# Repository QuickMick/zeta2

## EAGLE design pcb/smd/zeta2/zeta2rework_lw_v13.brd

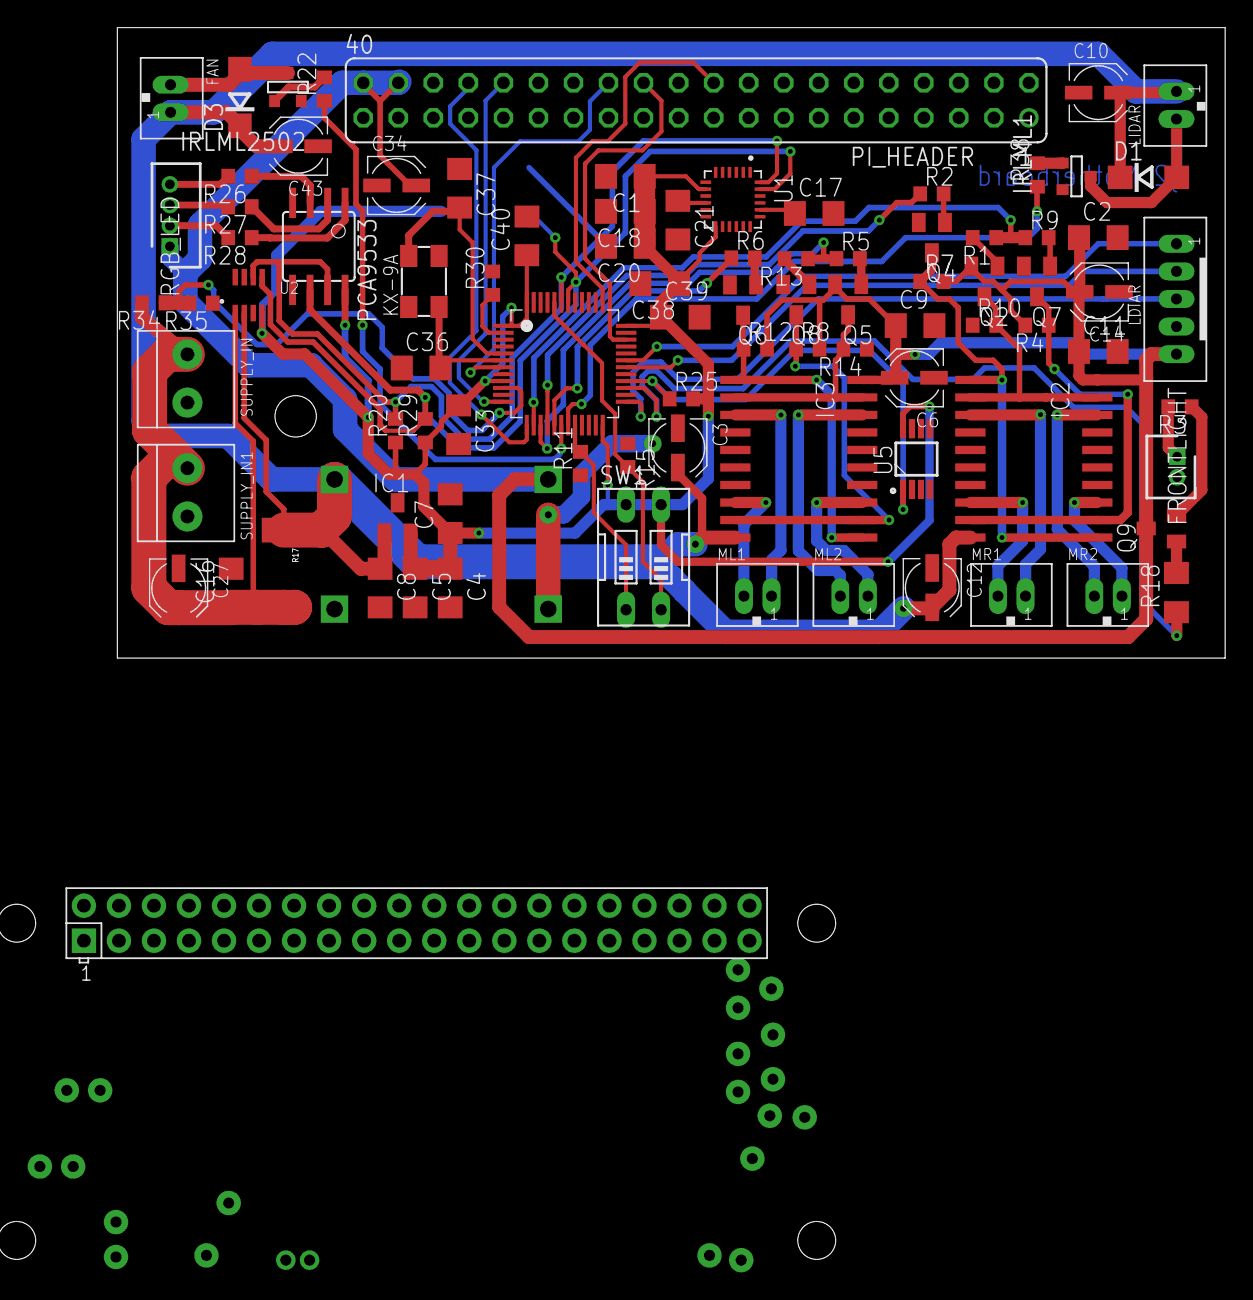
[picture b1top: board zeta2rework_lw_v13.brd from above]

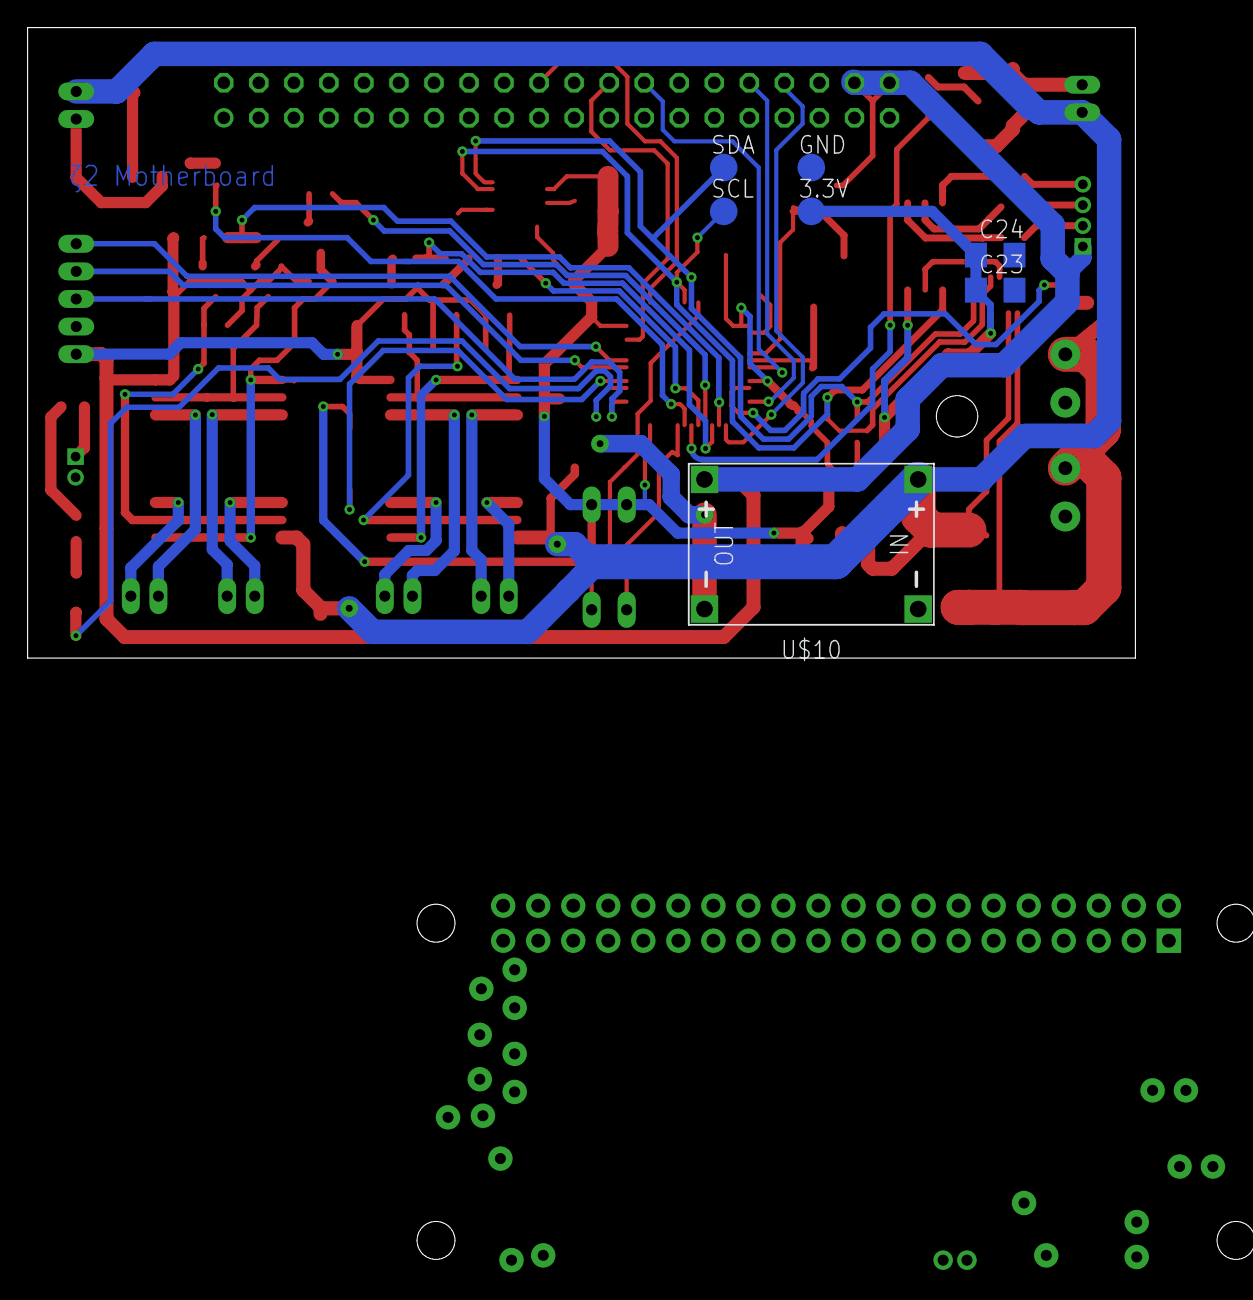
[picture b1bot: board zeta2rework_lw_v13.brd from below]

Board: 2 copper layers, 80.3 x 45.7 mm, 96 parts (7 on the bottom side), 64 nets.

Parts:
3.3V: TPSQTP20R; TP20R
C1, C4, C23, C36, C37: 10µF; C1206
C2, C9: 0.1nF; C1206
C3, C10, C12, C27, C34, C43: 47µF; UD-4X5,8_NICHICON
C5, C7, C11, C16, C18, C20, C21, C24: 0.1µF; C1206
C6, C14: 10µF; UD-4X5,8_NICHICON
C8: 4.7µF; C1206
C17: 2,2nF; C1206
C33, C38, C39, C40: 10nF; C1206
D1, D3: 1N4004 SMD; DO214AC
FAN: JST-PH_2-PIN_HEADER; JST_B2B-PH_HEADER
FRONTLIGHT: B2B-ZR(LF)(SN); SHDR2W50P0X150_1X2_450X350X450
GND: TPSQTP20R; TP20R
IC1: MAX6520; SOT23
IC2, IC3: L293DD; SO20
IRLML1, IRLML2502: SOT-23
KX-9A: 8Mhz; 5.0X3.2_KX-9A
LDIAR: JST-PH_5-PIN_HEADER; JST_B5B-PH_HEADER
LIDAR: JST-PH_2-PIN_HEADER; JST_B2B-PH_HEADER
ML1, ML2: JST-PH_2-PIN_HEADER; JST_B2B-PH_HEADER
MR1, MR2: JST-PH_2-PIN_HEADER; JST_B2B-PH_HEADER
PCA9533: PCA9533; SOIC8
PI_HEADER: FE20-2
Q2, Q4, Q5, Q6, Q7, Q8, Q9: SOT23
R1, R2, R5, R6, R9, R13: 500R; R0603
R3, R26, R27, R28: 220R; R0603
R4, R7, R8, R10, R12, R14, R30, R34: 100k; R0603
R11, R15: 132k; R0603
R17: 0.1/1% (PT2512FK-070R1L); 2512
R18: 500; R1206
R20, R29: 10k; R0603
R22, R38: 22R; R0603
R25: 4k7; R0603
R35: 69k; R0603
RGB_LED: B4B-ZR(LF)(SN); SHDR4W50P0X150_1X4_750X350X450
SCL: TPSQTP20R; TP20R
SDA: TPSQTP20R; TP20R
STM32F103CB: STM32F103CB; LQFP48_7X7MM_0.5MMPP
SUPPLY_IN, SUPPLY_IN1: TERMBLOCK_1X2-3.5MM; 1X2-3.5MM
SW1: EDG-02
U1: MPU-6050; QFN50P400X400X95-24N
U2: INA219; SOT23-8
U5: DS18B20U+; SOP65P490X95-8N
U$1: RPI-ZERO; RASP_PI_ZERO_BOARD_FULL
U$10: DC-DC-STEP-DOWN-MP2307

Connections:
+3V3: 3.3V.TP, C1.1, C4.1, C5.1, C7.1, C18.1, C20.1, C23.1, C24.1, C33.1, C38.1, C39.1, C40.1, IC1.2, PCA9533.8, R20.1, R25.2, R29.1, STM32F103CB.1, STM32F103CB.9, STM32F103CB.24, STM32F103CB.36, STM32F103CB.48, SW1.3, SW1.4, U1.8, U1.13, U2.4, U5.8
+5V: C2.1, C6.+, C9.1, C11.1, C14.+, C34.+, IC2.20, IC3.20, LDIAR.P5, PI_HEADER.38, PI_HEADER.40, Q2.2, Q5.2, Q9.3, R4.2, R7.2, R8.2, R12.2, RGB_LED.1, U$10.OUT+
+8V: C3.+, C8.1, C10.+, C12.+, C43.+, D1.C, D3.C, FAN.P1, IC1.1, IC2.10, IC3.10, LIDAR.P1, R17.1, U2.2, U$10.IN+
BAT_LVL: R34.1, R35.2, STM32F103CB.10
BOOT0: R15.2, STM32F103CB.44, SW1.2
BOOT1: R11.2, STM32F103CB.20, SW1.1
FRONT_LIGHT: R18.1, STM32F103CB.27
GND: C1.2, C2.2, C3.-, C4.2, C5.2, C6.-, C7.2, C8.2, C9.2, C10.-, C11.2, C12.-, C14.-, C16.2, C17.2, C18.2, C20.2, C21.2, C23.2, C24.2, C27.-, C33.2, C34.-, C36.1, C37.1, C38.2, C39.2, C40.2, C43.-, FRONTLIGHT.2, GND.TP, IC1.3, IC2.4, IC2.5, IC2.6, IC2.7, IC2.14, IC2.15, IC2.16, IC2.17, IC3.4, IC3.5, IC3.6, IC3.7, IC3.14, IC3.15, IC3.16, IC3.17, IRLML1.2, IRLML2502.2, LDIAR.P4, PCA9533.4, PI_HEADER.1, PI_HEADER.8, PI_HEADER.12, PI_HEADER.15, PI_HEADER.22, PI_HEADER.28, PI_HEADER.31, PI_HEADER.36, Q4.2, Q6.2, Q7.2, Q8.2, R10.1, R11.1, R14.1, R15.1, R30.2, R35.1, STM32F103CB.8, STM32F103CB.23, STM32F103CB.35, STM32F103CB.47, SUPPLY_IN.1, SUPPLY_IN1.1, U1.1, U1.9, U1.11, U1.18, U2.3, U2.7, U2.8, U5.4, U$10.IN-, U$10.OUT-
LIDAR_POS_INT: LDIAR.P3, STM32F103CB.25
M_DIR_1: R1.1, R9.1, STM32F103CB.14
M_DIR_2: R5.1, R13.1, STM32F103CB.15
unnamed: IC2.9, IC2.12, Q7.3, R4.1
unnamed: IC3.18, ML2.P2
unnamed: IC3.13, ML2.P1
unnamed: IC2.18, MR2.P2
unnamed: IC2.2, IC2.19, Q2.3, R10.2
unnamed: IC3.9, IC3.12, Q8.3, R8.1
unnamed: IC3.2, IC3.19, Q5.3, R14.2
unnamed: IC2.1, IC2.11, Q4.3, R7.1
unnamed: IC3.1, IC3.11, Q6.3, R12.1
unnamed: Q2.1, R1.2
unnamed: Q4.1, R2.2
unnamed: Q7.1, R9.2
unnamed: Q5.1, R5.2
unnamed: Q6.1, R6.2
unnamed: Q8.1, R13.2
unnamed: IC2.13, MR2.P1
unnamed: IC2.8, MR1.P2
unnamed: IC2.3, MR1.P1
unnamed: Q9.1, R18.2
unnamed: PCA9533.3, R26.1
unnamed: PCA9533.2, R27.1
unnamed: PCA9533.1, R28.1
unnamed: IC3.8, ML1.P2
unnamed: IC3.3, ML1.P1
unnamed: Q9.2, R3.1
unnamed: FRONTLIGHT.1, R3.2
unnamed: R26.2, RGB_LED.4
unnamed: R27.2, RGB_LED.3
unnamed: C17.1, U1.20
unnamed: R28.2, RGB_LED.2
unnamed: C21.1, U1.10
unnamed: IRLML2502.3, R22.2
unnamed: IRLML1.3, R38.2
unnamed: D1.A, IRLML1.1, LIDAR.P2
unnamed: C36.2, KX-9A.1, STM32F103CB.6
unnamed: C37.2, KX-9A.3, STM32F103CB.5
unnamed: R30.1, STM32F103CB.2
unnamed: D3.A, FAN.P2, IRLML2502.1
NRST: PI_HEADER.26, STM32F103CB.7
PWM_FAN: R22.1, STM32F103CB.18
PWM_LIDAR: R38.1, STM32F103CB.19
PWM_M_EN_1: R2.1, STM32F103CB.16
PWM_M_EN_2: R6.1, STM32F103CB.17
SCL: PCA9533.6, R29.2, SCL.TP, STM32F103CB.42, U1.23, U2.5
SDA: PCA9533.7, R20.2, SDA.TP, STM32F103CB.43, U1.24, U2.6
SWCLK: PI_HEADER.20, STM32F103CB.37
SWDIO: PI_HEADER.24, STM32F103CB.34
TEMPERATURE: R25.1, STM32F103CB.28, U5.1
U1_RX: LDIAR.P1, STM32F103CB.31
U1_TX: LDIAR.P2, STM32F103CB.30
USART2_RX: PI_HEADER.34, STM32F103CB.13
USART2_TX: PI_HEADER.32, STM32F103CB.12
V+: C16.1, C27.+, R17.2, R34.2, SUPPLY_IN.2, SUPPLY_IN1.2, U2.1

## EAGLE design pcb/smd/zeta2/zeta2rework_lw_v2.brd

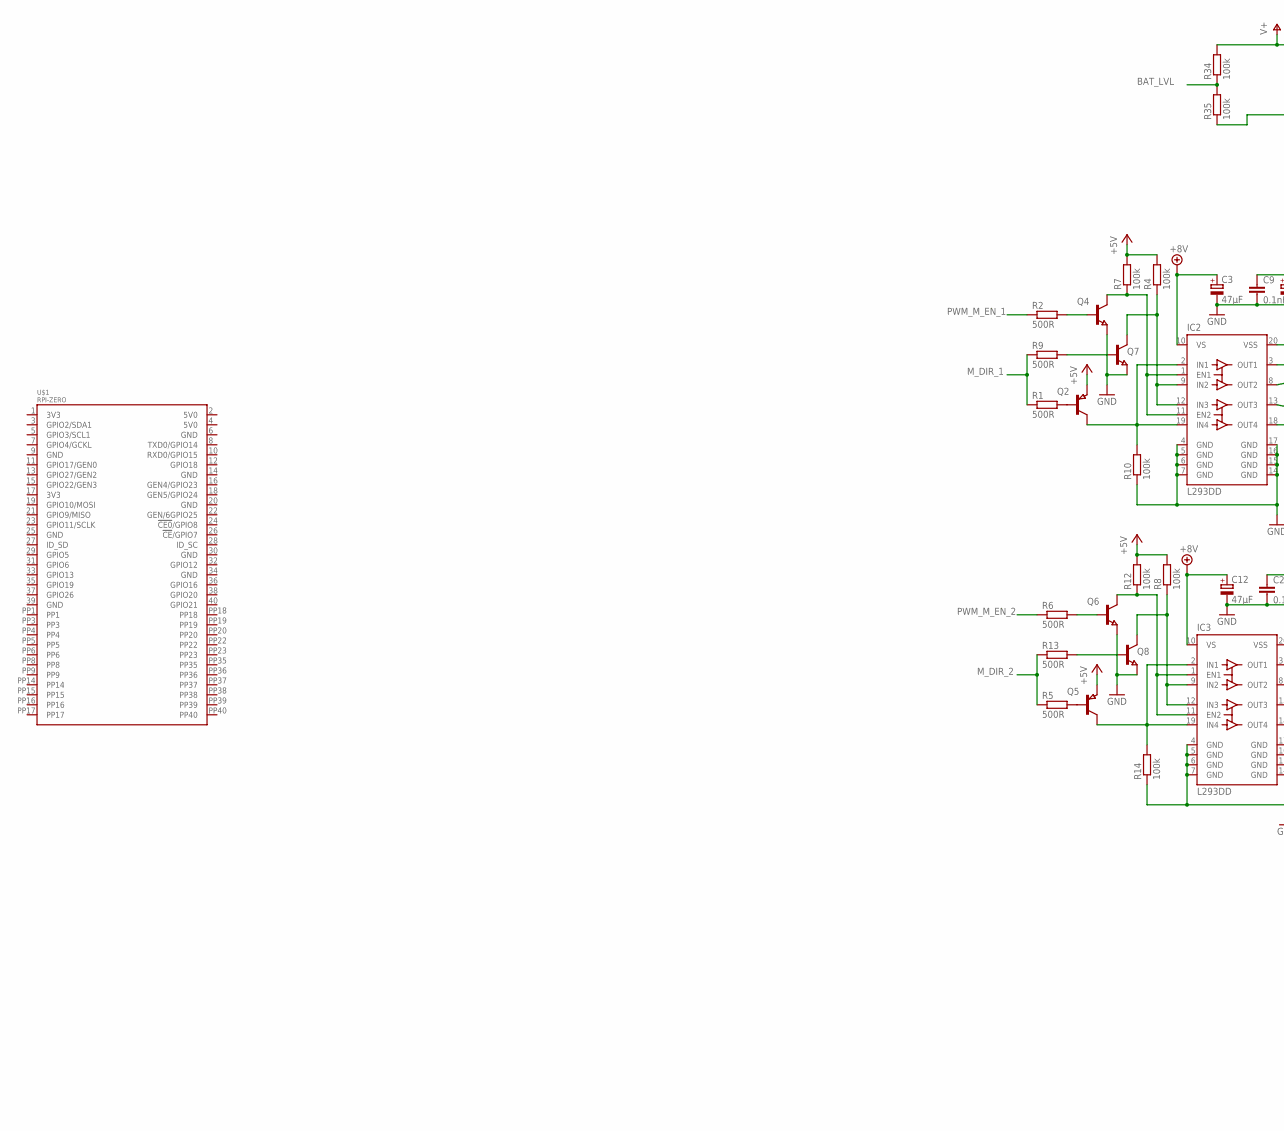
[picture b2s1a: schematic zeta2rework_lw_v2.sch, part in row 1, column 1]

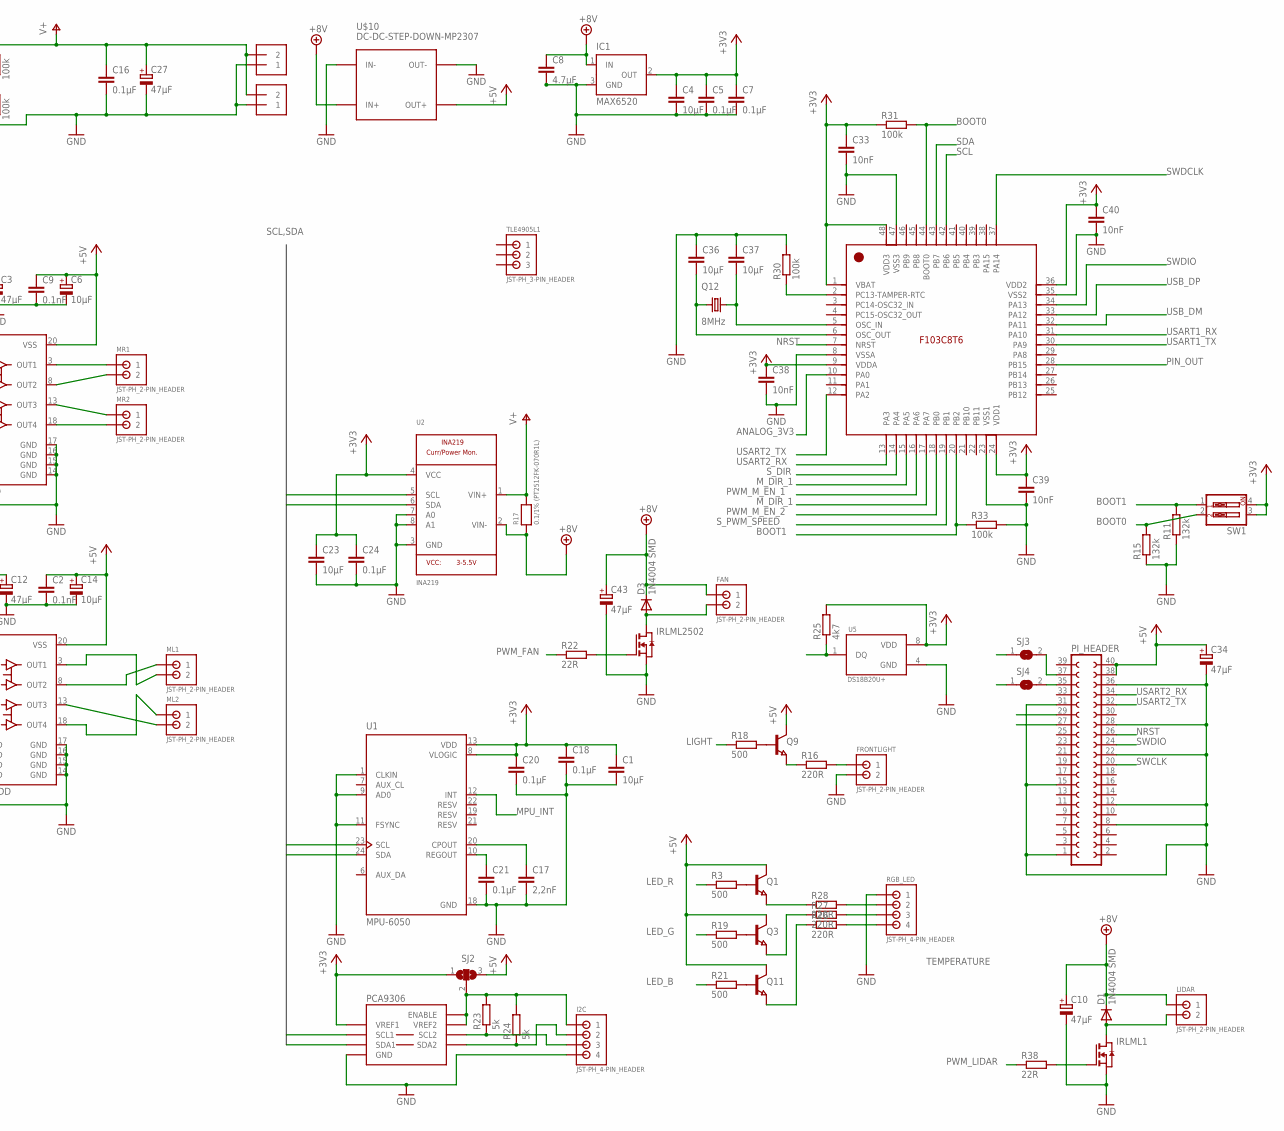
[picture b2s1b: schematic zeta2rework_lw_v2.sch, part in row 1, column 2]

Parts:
C1, C4, C23, C36, C37: 10µF; C1206
C2, C9: 0.1nF; C1206
C3, C10, C12, C27, C34, C43: 47µF; UD-4X5,8_NICHICON
C5, C7, C16, C18, C20, C21, C24: 0.1µF; C1206
C6, C14: 10µF; UD-4X5,8_NICHICON
C8: 4.7µF; C1206
C17: 2,2nF; C1206
C33, C38, C39, C40: 10nF; C1206
D1, D3: 1N4004 SMD; MELF-MLL41
FAN: JST-PH_2-PIN_HEADER; JST_B2B-PH_HEADER
FRONTLIGHT: JST-PH_2-PIN_HEADER; JST_B2B-PH_HEADER
I2C: JST-PH_4-PIN_HEADER; JST_B4B-PH_HEADER
IC1: MAX6520; SOT23
IC2, IC3: L293DD; SO20
IRLML1, IRLML2502: NMOSSOT23; SOT-23
LIDAR: JST-PH_2-PIN_HEADER; JST_B2B-PH_HEADER
ML1, ML2: JST-PH_2-PIN_HEADER; JST_B2B-PH_HEADER
MR1, MR2: JST-PH_2-PIN_HEADER; JST_B2B-PH_HEADER
PCA9306: IC2_LEVEL_TRANSLATER; SOIC-8
PI_HEADER: FE20-2
Q1, Q3, Q4, Q6, Q7, Q8, Q9, Q11: NPN-TRANSISTOR_SOT23; SOT23
Q2, Q5: PNP-TRANSISTOR_SOT23; SOT23
Q12: 8MHz; 7.0X5.0
R1, R2, R5, R6, R9, R13: 500R; R0603
R3, R18, R19: 500; R1206
R4, R7, R8, R10, R12, R14, R30, R31, R33, R34, R35: 100k; R0603
R11, R15: 132k; R0603
R16, R26, R27, R28: 220R; R0603
R17: 0.1/1% (PT2512FK-070R1L); 2512
R21: 500; R0603
R22, R38: 22R; R0603
R23, R24: 5k; R0603
R25: 4k7; R0603
RGB_LED: JST-PH_4-PIN_HEADER; JST_B4B-PH_HEADER
SJ2: SJ2W; SJ_2
SJ3, SJ4: SOLDERJUMPERREFLOW_NOPASTE; SOLDERJUMPER_REFLOW_NOPASTE
SUPPLY_IN, SUPPLY_IN1: TERMBLOCK_1X2-3.5MM; 1X2-3.5MM
SW1: SW_DIP-2; EDG-02
TLE4905L1: JST-PH_3-PIN_HEADER; JST_B3B-PH_HEADER
U1: MPU-6050; QFN50P400X400X95-24N
U2: INA219; SOT23-8
U5: DS18B20U+; SOP65P490X95-8N
U$1: RPI-ZERO; RASP_PI_ZERO_BOARD_FULL
U$4: STM32F103C8T6; LQFP48_7X7MM_0.5MMPP
U$10: DC-DC-STEP-DOWN-MP2307

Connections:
+3V3: C1.1, C4.1, C5.1, C7.1, C18.1, C20.1, C23.1, C24.1, C33.1, C38.1, C39.1, C40.1, IC1.2 (OUT), PCA9306.1 (VREF1), R25.2, R31.1, SJ2.1, SW1.3, SW1.4, U1.8 (VLOGIC), U1.13 (VDD), U2.4 (VCC), U5.8 (VDD), U$4.1 (VBAT), U$4.9 (VDDA), U$4.24 (VDD1), U$4.36 (VDD2), U$4.48 (VDD3)
+5V: C2.1, C6.+, C9.1, C14.+, C34.+, IC2.20 (VSS), IC3.20 (VSS), PI_HEADER.38, PI_HEADER.40, Q1.3 (C), Q2.2 (E), Q3.3 (C), Q5.2 (E), Q9.3 (C), Q11.3 (C), R4.2, R7.2, R8.2, R12.2, SJ2.3, U$10.OUT+
+8V: C3.+, C8.1, C10.+, C12.+, C43.+, D1.C, D3.C, FAN.P1 (1), IC1.1 (IN), IC2.10 (VS), IC3.10 (VS), LIDAR.P1 (1), R17.1, U2.2 (VIN-), U$10.IN+
ANALOG_3V3: U$4.10 (PA0)
BAT_LVL: R34.1, R35.2
BOOT0: R15.2, R31.2, SW1.2, U$4.44 (BOOT0)
BOOT1: R11.2, R33.1, SW1.1, U$4.20 (PB2)
BOOT2: PI_HEADER.29
BOOT3: PI_HEADER.27
GND: C1.2, C2.2, C3.-, C4.2, C5.2, C6.-, C7.2, C8.2, C9.2, C10.-, C12.-, C14.-, C16.2, C17.2, C18.2, C20.2, C21.2, C23.2, C24.2, C27.-, C33.2, C34.-, C36.1, C37.1, C38.2, C39.2, C40.2, C43.-, FRONTLIGHT.P2 (2), I2C.P4 (4), IC1.3 (GND), IC2.4 (GND), IC2.5 (GND), IC2.6 (GND), IC2.7 (GND), IC2.14 (GND), IC2.15 (GND), IC2.16 (GND), IC2.17 (GND), IC3.4 (GND), IC3.5 (GND), IC3.6 (GND), IC3.7 (GND), IC3.14 (GND), IC3.15 (GND), IC3.16 (GND), IC3.17 (GND), IRLML1.2 (S), IRLML2502.2 (S), PCA9306.4 (GND), PI_HEADER.1, PI_HEADER.8, PI_HEADER.12, PI_HEADER.15, PI_HEADER.22, PI_HEADER.28, PI_HEADER.31, PI_HEADER.36, Q4.2 (E), Q6.2 (E), Q7.2 (E), Q8.2 (E), R10.1, R11.1, R14.1, R15.1, R30.2, R33.2, R35.1, RGB_LED.P1 (1), SUPPLY_IN.1, SUPPLY_IN1.1, U1.1 (CLKIN), U1.9 (AD0), U1.11 (FSYNC), U1.18 (GND), U2.3 (GND), U2.7 (A0), U2.8 (A1), U5.4 (GND), U$4.8 (VSSA), U$4.23 (VSS1), U$4.35 (VSS2), U$4.47 (VSS3), U$10.IN-, U$10.OUT-
LED_B: R21.1
LED_G: R19.1
LED_R: R3.1
LIGHT: R18.1
MPU_INT: U1.12 (INT)
M_DIR_1: R1.1, R9.1, U$4.15 (PA5), U$4.17 (PA7)
M_DIR_2: R5.1, R13.1
unnamed: IC2.9 (IN2), IC2.12 (IN3), Q7.3 (C), R4.1
unnamed: IC3.18 (OUT4), ML2.P1 (1)
unnamed: IC3.13 (OUT3), ML2.P2 (2)
unnamed: IC2.18 (OUT4), MR2.P2 (2)
unnamed: IC2.2 (IN1), IC2.19 (IN4), Q2.3 (C), R10.2
unnamed: IC3.9 (IN2), IC3.12 (IN3), Q8.3 (C), R8.1
unnamed: IC3.2 (IN1), IC3.19 (IN4), Q5.3 (C), R14.2
unnamed: IC2.1 (EN1), IC2.11 (EN2), Q4.3 (C), R7.1
unnamed: IC3.1 (EN1), IC3.11 (EN2), Q6.3 (C), R12.1
unnamed: Q2.1 (B), R1.2
unnamed: Q4.1 (B), R2.2
unnamed: Q7.1 (B), R9.2
unnamed: Q5.1 (B), R5.2
unnamed: Q6.1 (B), R6.2
unnamed: Q8.1 (B), R13.2
unnamed: IC2.13 (OUT3), MR2.P1 (1)
unnamed: IC2.8 (OUT2), MR1.P2 (2)
unnamed: IC2.3 (OUT1), MR1.P1 (1)
unnamed: Q9.1 (B), R18.2
unnamed: Q9.2 (E), R16.1
unnamed: FRONTLIGHT.P1 (1), R16.2
unnamed: Q1.1 (B), R3.2
unnamed: Q3.1 (B), R19.2
unnamed: Q1.2 (E), R28.1
unnamed: IC3.8 (OUT2), ML1.P1 (1)
unnamed: IC3.3 (OUT1), ML1.P2 (2)
unnamed: Q3.2 (E), R27.1
unnamed: Q11.2 (E), R26.1
unnamed: R26.2, RGB_LED.P4 (4)
unnamed: Q11.1 (B), R21.2
unnamed: R27.2, RGB_LED.P3 (3)
unnamed: C17.1, U1.20 (CPOUT)
unnamed: R28.2, RGB_LED.P2 (2)
unnamed: C21.1, U1.10 (REGOUT)
unnamed: IRLML2502.3 (G), R22.2
unnamed: IRLML1.3 (G), R38.2
unnamed: D1.A, IRLML1.1 (D), LIDAR.P2 (2)
unnamed: I2C.P1 (1), PCA9306.7 (VREF2), PCA9306.8 (ENABLE), R23.2, R24.2, SJ2.2
unnamed: I2C.P3 (3), PCA9306.6 (SCL2), R23.1
unnamed: I2C.P2 (2), PCA9306.5 (SDA2), R24.1
unnamed: PI_HEADER.37, SJ3.2
unnamed: PI_HEADER.35, SJ4.2
unnamed: C36.2, Q12.1, U$4.6 (OSC_OUT)
unnamed: C37.2, Q12.3 (2), U$4.5 (OSC_IN)
unnamed: R30.1, U$4.2 (PC13-TAMPER-RTC)
unnamed: D3.A, FAN.P2 (2), IRLML2502.1 (D)
NRST: PI_HEADER.26, U$4.7 (NRST)
PIN_OUT: U$4.28 (PB15)
PWM_FAN: R22.1
PWM_LIDAR: R38.1
PWM_M_EN_1: R2.1, U$4.16 (PA6)
PWM_M_EN_2: R6.1, U$4.18 (PB0)
SCL: U1.23 (SCL), U2.5 (SCL), U$4.42 (PB6)
SCL2: PCA9306.2 (SCL1)
SCL3: SJ4.1
SDA: U1.24 (SDA), U2.6 (SDA), U$4.43 (PB7)
SDA2: PCA9306.3 (SDA1)
SDA3: SJ3.1
SWCLK: PI_HEADER.20
SWDCLK: U$4.37 (PA14)
SWDIO: PI_HEADER.24, U$4.34 (PA13)
S_DIR: U$4.14 (PA4)
S_PWM_SPEED: U$4.19 (PB1)
TEMPERATURE: R25.1, U5.1 (DQ)
USART1_RX: U$4.31 (PA10)
USART1_TX: U$4.30 (PA9)
USART2_RX: PI_HEADER.34, U$4.13 (PA3)
USART2_TX: PI_HEADER.32, U$4.12 (PA2)
USB_DM: U$4.32 (PA11)
USB_DP: U$4.33 (PA12)
V+: C16.1, C27.+, R17.2, R34.2, SUPPLY_IN.2, SUPPLY_IN1.2, U2.1 (VIN+)

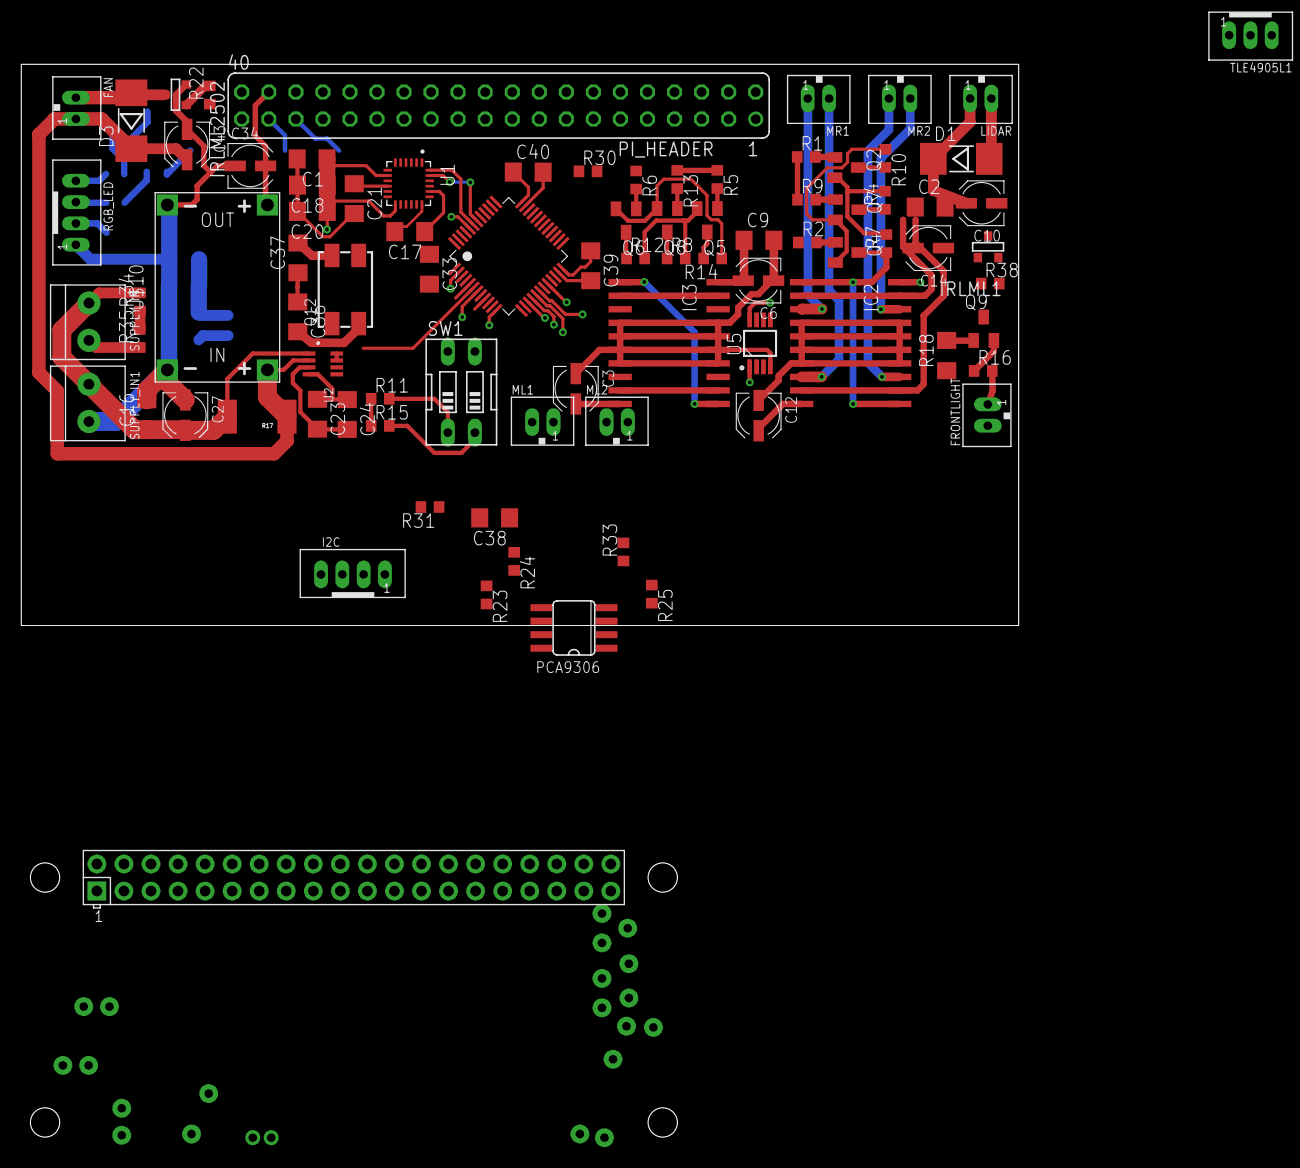
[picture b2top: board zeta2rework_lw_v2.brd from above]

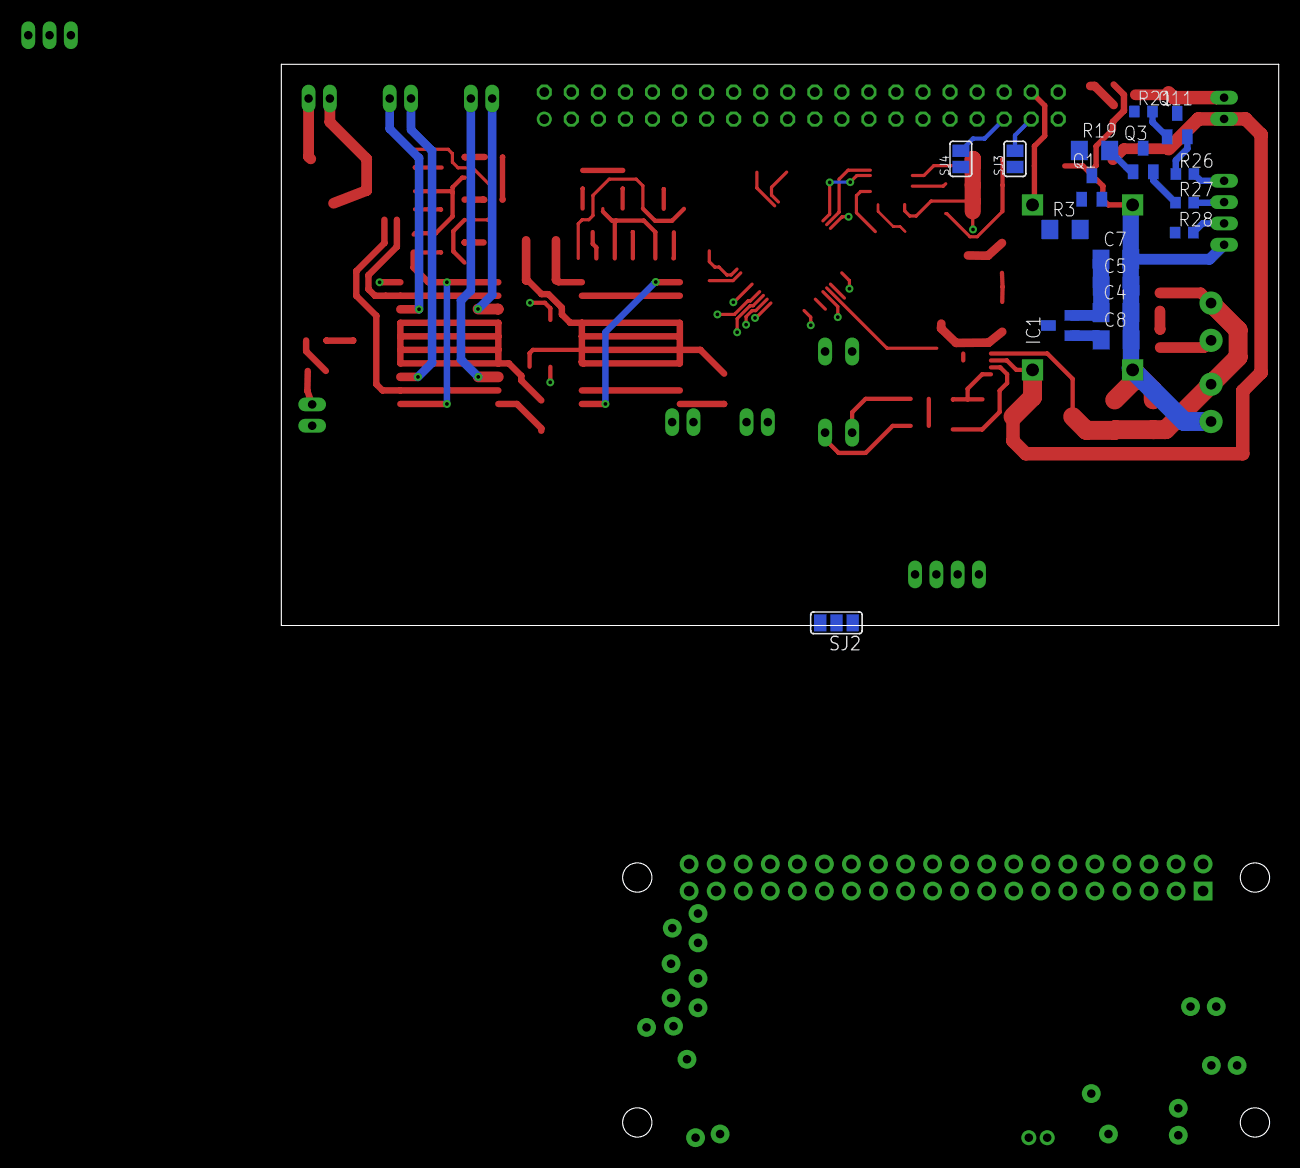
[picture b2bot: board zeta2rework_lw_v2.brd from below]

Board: 2 copper layers, 93.6 x 52.7 mm, 103 parts (17 on the bottom side), 65 nets.

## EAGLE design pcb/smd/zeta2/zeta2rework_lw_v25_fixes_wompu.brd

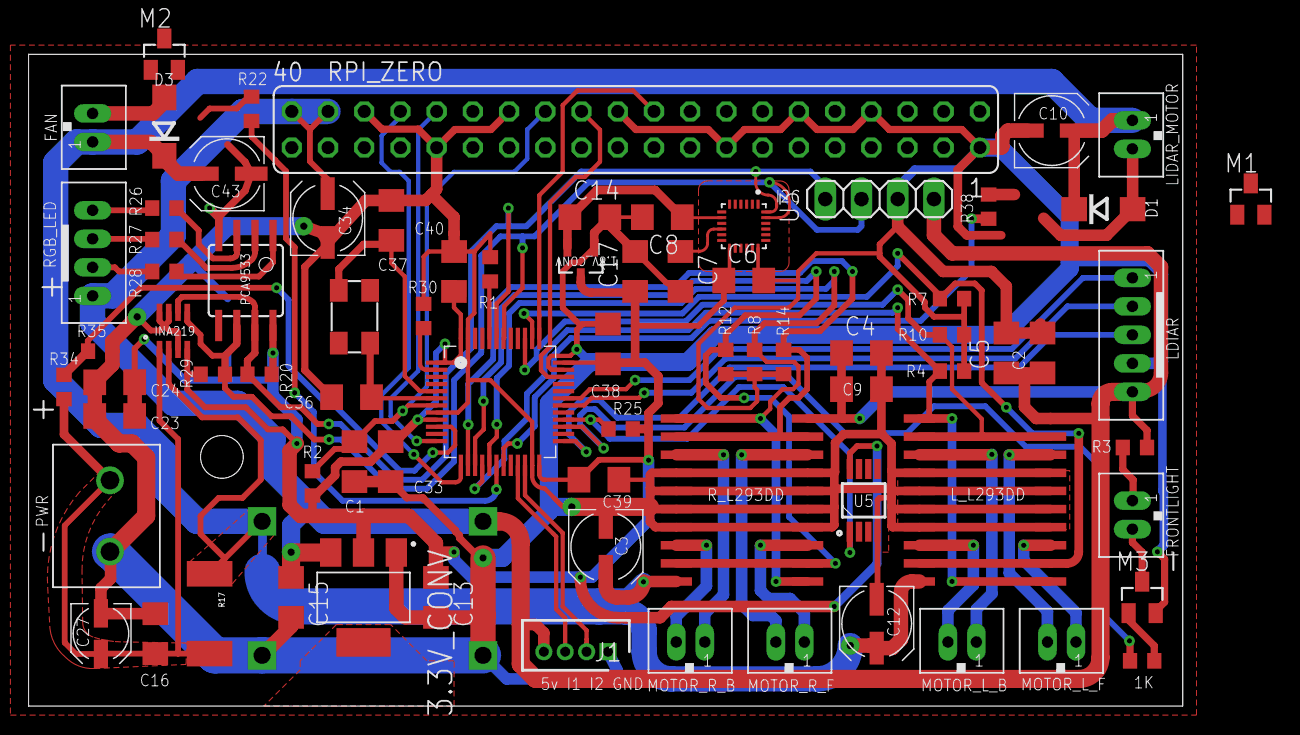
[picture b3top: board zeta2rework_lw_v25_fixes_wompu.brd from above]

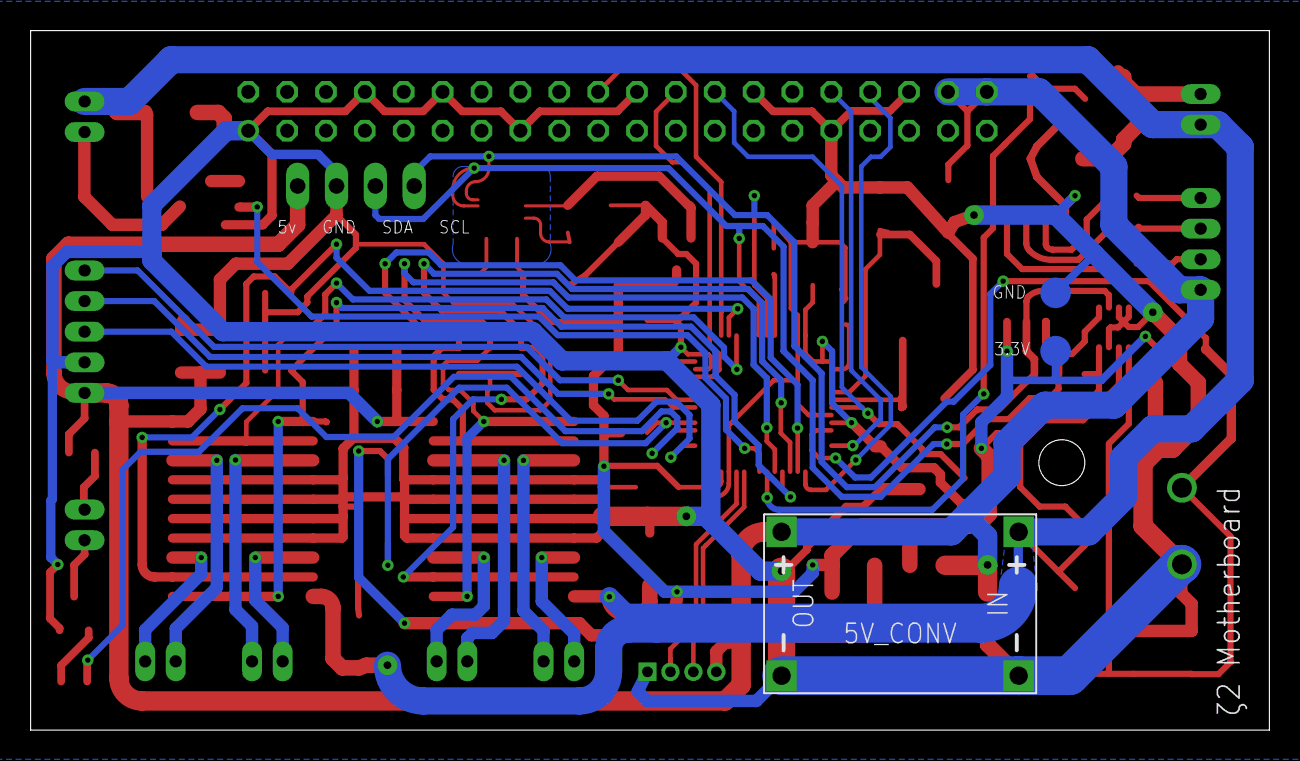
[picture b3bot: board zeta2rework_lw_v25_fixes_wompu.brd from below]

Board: 2 copper layers, 81.0 x 45.7 mm, 80 parts (3 on the bottom side), 55 nets.

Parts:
1.8V_CONV: MCP1700T-1802E/TT; SOT95P237X112-3N
1K: 22R; R0603
3.3V: TPSQTP20R; TP20R
3.3V_CONV: NCP1117LPST33T3G; SOT230P700X175-4N
5V_CONV: DC-DC-STEP-DOWN-MP2307
C1: 100nF; C1206
C2, C6, C7, C8, C9: 0.1nF; C1206
C3, C10, C12, C34, C43: 47µF; UD-5X5,8_NICHICON
C4, C5, C33, C38, C39, C40: 10nF; C1206
C13, C15: 10µF; C1206
C14, C17: 1µF; C1206
C16, C24: 0.1µF; C1206
C23: 100nf; C1206
C27: 100µF; UD-4X5,8_NICHICON
C36, C37: 7pf; C1206
D1, D3: 1N4004 SMD; DO214AC
FAN: JST-PH_2-PIN_HEADER; JST_B2B-PH_HEADER
FRONTLIGHT: JST-PH_2-PIN_HEADER; JST_B2B-PH_HEADER
GND: TPSQTP20R; TP20R
I2C: 1X04
INA219: INA219; SOT23-8
J1: B4B-ZR(LF)(SN); SHDR4W50P0X150_1X4_750X350X450
KX-9A: 8Mhz; 5.0X3.2_KX-9A
LDIAR: JST-PH_5-PIN_HEADER; JST_B5B-PH_HEADER
LIDAR_MOTOR: JST-PH_2-PIN_HEADER; JST_B2B-PH_HEADER
L_L293DD: L293DD; SO20
M1, M2, M3: IRLML2502; SOT23
MOTOR_L_B: JST-PH_2-PIN_HEADER; JST_B2B-PH_HEADER
MOTOR_L_F: JST-PH_2-PIN_HEADER; JST_B2B-PH_HEADER
MOTOR_R_B: JST-PH_2-PIN_HEADER; JST_B2B-PH_HEADER
MOTOR_R_F: JST-PH_2-PIN_HEADER; JST_B2B-PH_HEADER
PCA9533: PCA9533; SOIC8
PWR: 691137710002
R1, R2, R4, R7, R8, R10, R12, R14, R20, R29: 10k; R0603
R3: 0R; R0603
R17: 0.1/1% (PT2512FK-070R1L); 2512
R22, R38: 22R; R0603
R25: 4k7; R0603
R26, R27, R28: 220R; R0603
R30, R34: 100k; R0603
R35: 69k; R0603
RGB_LED: JST-PH_4-PIN_HEADER; JST_B4B-PH_HEADER
RPI_ZERO: FE20-2
R_L293DD: L293DD; SO20
STM32F103CB: STM32F103CB; LQFP48_7X7MM_0.5MMPP
U3: ICM-20948; QFN40P300X300X105-25N
U5: DS18B20U+; SOP65P490X95-8N

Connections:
+1.8V: 1.8V_CONV.2, C8.1, C14.1, U3.8
+3V3: 1.8V_CONV.3, 3.3V.TP, 3.3V_CONV.2, 3.3V_CONV.4, C6.1, C13.1, C17.1, C23.1, C24.1, C33.1, C38.1, C39.1, C40.1, INA219.4, PCA9533.8, R2.2, R20.1, R25.2, R29.1, STM32F103CB.1, STM32F103CB.9, STM32F103CB.24, STM32F103CB.36, STM32F103CB.48, U3.13, U5.8
+5V: 3.3V_CONV.3, 5V_CONV.OUT+, C2.1, C4.1, C5.1, C9.1, C15.1, C34.+, I2C.4, J1.4, LDIAR.P5, L_L293DD.20, R3.1, RGB_LED.P1, RPI_ZERO.38, RPI_ZERO.40, R_L293DD.20
+8V: 5V_CONV.IN+, C3.+, C10.+, C12.+, C43.+, D1.C, D3.C, FAN.P1, INA219.2, LIDAR_MOTOR.P1, L_L293DD.10, R17.1, R_L293DD.10
BAT_LVL: R34.1, R35.2, STM32F103CB.10
FRONT_LIGHT: 1K.1, STM32F103CB.27
GND: 1.8V_CONV.1, 3.3V_CONV.1, 5V_CONV.IN-, 5V_CONV.OUT-, C1.2, C2.2, C3.-, C4.2, C5.2, C6.2, C7.2, C8.2, C9.2, C10.-, C12.-, C13.2, C14.2, C15.2, C16.2, C17.2, C23.2, C24.2, C27.-, C33.2, C34.-, C36.1, C37.1, C38.2, C39.2, C40.2, C43.-, GND.TP, I2C.3, INA219.3, INA219.7, INA219.8, J1.1, LDIAR.P4, L_L293DD.4, L_L293DD.5, L_L293DD.6, L_L293DD.7, L_L293DD.14, L_L293DD.15, L_L293DD.16, L_L293DD.17, M1.2, M2.2, M3.2, PCA9533.4, PWR.2, R1.2, R4.1, R7.1, R8.1, R10.1, R12.1, R14.1, R30.2, R35.1, RPI_ZERO.1, RPI_ZERO.8, RPI_ZERO.12, RPI_ZERO.15, RPI_ZERO.22, RPI_ZERO.28, RPI_ZERO.31, RPI_ZERO.36, R_L293DD.4, R_L293DD.5, R_L293DD.6, R_L293DD.7, R_L293DD.14, R_L293DD.15, R_L293DD.16, R_L293DD.17, STM32F103CB.8, STM32F103CB.23, STM32F103CB.35, STM32F103CB.47, U3.18, U5.4
INT_MD_1: J1.3, STM32F103CB.21
INT_MD_2: J1.2, STM32F103CB.22
LIDAR_POS_INT: LDIAR.P3, STM32F103CB.25
M_DIR_L_1: L_L293DD.2, L_L293DD.19, R10.2, STM32F103CB.39
M_DIR_L_2: L_L293DD.9, L_L293DD.12, R7.2, STM32F103CB.38
M_DIR_R_1: R14.2, R_L293DD.2, R_L293DD.19, STM32F103CB.14
M_DIR_R_2: R12.2, R_L293DD.9, R_L293DD.12, STM32F103CB.15
unnamed: MOTOR_R_B.P2, R_L293DD.8
unnamed: MOTOR_R_F.P2, R_L293DD.18
unnamed: MOTOR_R_F.P1, R_L293DD.13
unnamed: L_L293DD.18, MOTOR_L_F.P2
unnamed: R1.1, STM32F103CB.44
unnamed: FRONTLIGHT.P1, R3.2
unnamed: C7.1, U3.10
unnamed: FRONTLIGHT.P2, M3.3
unnamed: 1K.2, M3.1
unnamed: L_L293DD.13, MOTOR_L_F.P1
unnamed: L_L293DD.8, MOTOR_L_B.P2
unnamed: L_L293DD.3, MOTOR_L_B.P1
unnamed: PCA9533.3, R26.1
unnamed: PCA9533.2, R27.1
unnamed: PCA9533.1, R28.1
unnamed: MOTOR_R_B.P1, R_L293DD.3
unnamed: R26.2, RGB_LED.P4
unnamed: R27.2, RGB_LED.P3
unnamed: R28.2, RGB_LED.P2
unnamed: M2.1, R22.2
unnamed: M1.1, R38.2
unnamed: D1.A, LIDAR_MOTOR.P2, M1.3
unnamed: C36.2, KX-9A.1, STM32F103CB.6
unnamed: C37.2, KX-9A.3, STM32F103CB.5
unnamed: R30.1, STM32F103CB.2
unnamed: D3.A, FAN.P2, M2.3
NRST: C1.1, R2.1, RPI_ZERO.26, STM32F103CB.7
PWM_FAN: R22.1, STM32F103CB.18
PWM_LIDAR: R38.1, STM32F103CB.19
PWM_M_EN_L: L_L293DD.1, L_L293DD.11, R4.2, STM32F103CB.16
PWM_M_EN_R: R8.2, R_L293DD.1, R_L293DD.11, STM32F103CB.17
SCL: I2C.2, INA219.5, PCA9533.6, R29.2, STM32F103CB.42, U3.23
SDA: I2C.1, INA219.6, PCA9533.7, R20.2, STM32F103CB.43, U3.24
SWCLK: RPI_ZERO.20, STM32F103CB.37
SWDIO: RPI_ZERO.24, STM32F103CB.34
TEMPERATURE: R25.1, STM32F103CB.28, U5.1
U1_RX: LDIAR.P1, STM32F103CB.31
U1_TX: LDIAR.P2, STM32F103CB.30
USART2_RX: RPI_ZERO.34, STM32F103CB.13
USART2_TX: RPI_ZERO.32, STM32F103CB.12
V+: C16.1, C27.+, INA219.1, PWR.1, R17.2, R34.2

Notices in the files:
parts and their libraries:
diy-modules: Released under the Creative Commons Attribution 4.0 International License: http://creativecommons.org/licenses/by/4.0
crystal-geyer_V1_0: Copyright: Geyer-Electronic
